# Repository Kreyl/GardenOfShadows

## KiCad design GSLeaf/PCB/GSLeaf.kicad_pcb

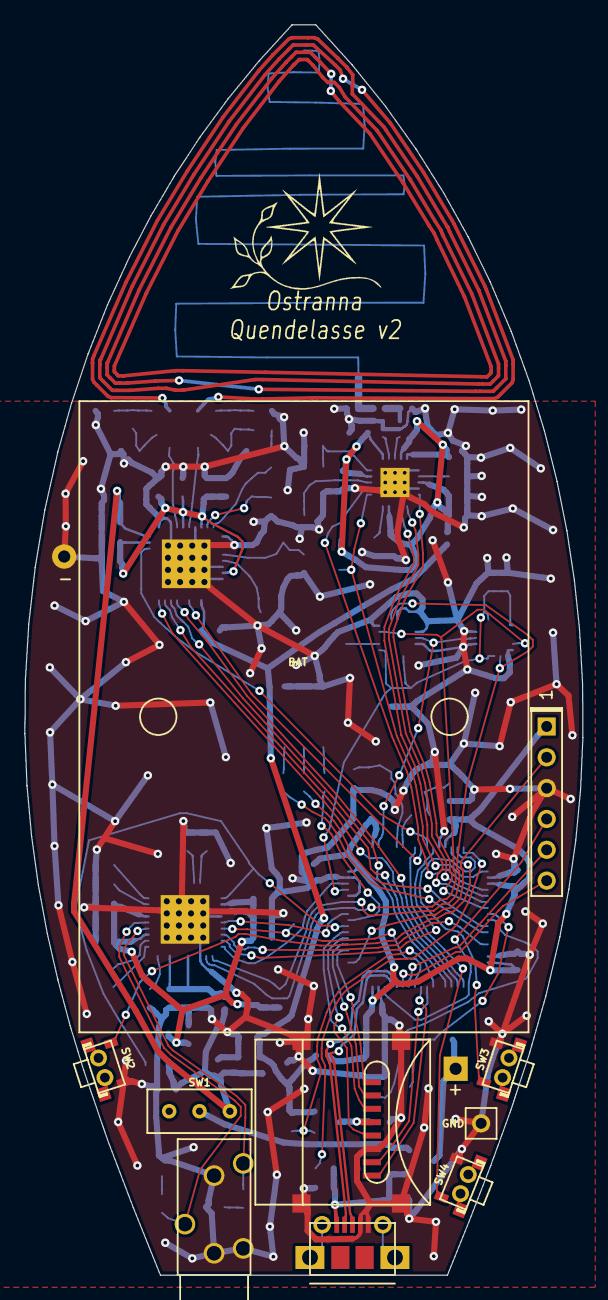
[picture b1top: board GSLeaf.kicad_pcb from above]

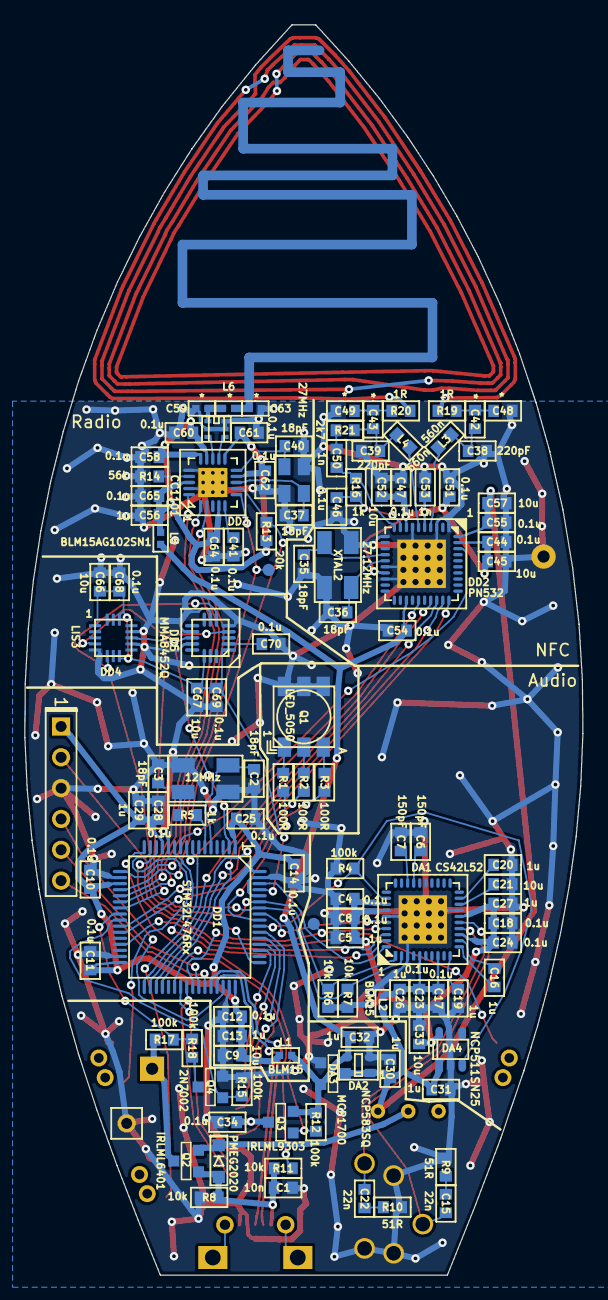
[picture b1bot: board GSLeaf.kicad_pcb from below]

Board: 2 copper layers, 46.0 x 103.0 mm, 129 parts (119 on the bottom side), 94 nets.

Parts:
ANT1: ANT_PCB_MONO; ANT_868_SEIDHE
B1: BAT; BATTERY_AAA_X3
BLN1: BALUN868JOHANSON; BALUN_JOHANSON868
C1: 10n; CAP_0603
C2, C3, C35, C36, C37, C40: 18pF; CAP_0603
C4, C8, C10, C11, C12, C14, C17, C18, C23, C24, C25, C28, C34, C41, C44, C46, C47, C51, C54, C55, C58, C60, C61, C62, C64, C65, C68, C69, C70: 0.1u; CAP_0603
C5, C13, C16, C19, C20, C26, C27, C29, C30, C31, C32, C56: 1u; CAP_0603
C6, C7: 150pF; CAP_0603
C9, C21, C33, C45, C52, C57, C66, C67: 10u; CAP_0603
C15, C22: 22n; CAP_0603
C38, C39: 220pF; CAP_0603
C42, C43, C48, C49: *; CAP_0603
C50, C53: 1n; CAP_0603
C59, C63: *; CAP_0402
D1: PMEG2020; SOD323
DA1: CS42L52; QFN40
DA2: NCP583SQ; SC82AB
DA3: MCP1700; SOT23-3
DA4: NCP511SN25; SOT23-5
DD1: STM32L476Rx; LQFP64
DD2: PN532; QFN40
DD3: CC1101; QFN20
DD4: LIS3; LGA16_3X3_5_3
DD5: MMA8452Q; QFN16_5x3
L1, L2: BLM15; IND_0402
L3, L4: 560n; IND_0603
L5: BLM15AG102SN1; IND_0402
L6: *; IND_0402
Logo1: Logo; Ostranna_12d7_10d1
Q1: LED_5050
Q2: IRLML6401; SOT23-3
Q3: IRLML9303; SOT23-3
Q4: 2N7002; SOT23-3
R1, R2, R3: 100R; RES_0603
R4, R12, R15, R17, R18: 100k; RES_0603
R5, R16: 1k; RES_0603
R6, R7, R8, R11: 10k; RES_0603
R9, R10: 51R; RES_0603
R13: 20k; RES_0603
R14: 56k; RES_0603
R19, R20: 1R; RES_0603
R21: 2k7; RES_0603
SW1: SWITCH; SW_SS-1P2T
SW2, SW3, SW4: BTN; BTN_IT1198
TP1, TP2: TESTPOINT; TESTPOINT_1MM
XL1: CONN_6; PLS-6
XL2: USB_MINI_B; USBmicro_MOLEX_1050170001
XL3: AudioJackSimple; AUDIO_CKX3_5_30
XL4: CONN_MICROSD; MICROSD_CAP_FIX05A
XL5: CONN_1; PLS-1Rnd
XTAL1: 12MHz; 0503x4-4
XTAL2: 27.12MHz; 0503x4-4
XTAL3: 27MHz; 03225C4

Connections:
+3.3V: C32.1, C54.1, DA2.3, DA3.2, DD2.23, L1.2, L5.2, Q3.2, R12.1
+5V: C1.2, D1.A, Q2.1, R8.1, R11.2, XL2.1
+BATT: B1.A, Q2.3, R17.1
/ACC_INT1: DD1.2, DD4.11, DD5.11
/ACC_PWR: C66.1, C67.1, C68.1, C69.1, DD1.61, DD4.1, DD4.14, DD5.1, DD5.14
/ANT1: BLN1.1, C59.1, L6.2
/ANT01: DD2.4, L3.2
/ANT2: ANT1.1, C63.1, L6.1
/ANT02: DD2.6, L4.2
/AU_LRCK: DA1.40, DD1.62
/AU_MCLK: DA1.37, DD1.41, TP1.1
/AU_RST: DA1.32, DA4.3, DD1.55, R4.2
/AU_SCLK: DA1.38, DD1.29
/AU_SDIN: DA1.39, DD1.11
/AU_SDOUT: DA1.36, DD1.57
/Antenna: R19.2, R20.2
/BAT_MEAS: DD1.24, R17.2, R18.1
/BLUE_LED: DD1.56, R1.2
/BTN_COM: DD1.14, SW2.1
/BTN_DOWN: DD1.8, SW4.1
/BTN_UP: DD1.15, SW3.1
/CC_CS: DD1.20, DD3.7, R13.1
/CC_GDO0: DD1.17, DD3.6, TP2.1
/CC_MISO: DD1.22, DD3.2
/CC_MOSI: DD1.23, DD3.20
/CC_SCK: DD1.21, DD3.1
/D+: DD1.45, XL2.3
/D-: DD1.44, XL2.2
/GREEN_LED: DD1.27, R3.2
/HP_OUTA: C15.2, DA1.15, XL3.2
/HP_OUTB: C22.2, DA1.14, XL3.3
/MEASURE_EN: DD1.25, Q4.1, R15.2
/PN_IRQ: DD1.9, DD2.25
/PN_MISO: DD1.35, DD2.29
/PN_MOSI: DD1.36, DD2.28
/PN_NSS: DD1.33, DD2.27
/PN_RESET: DD1.10, DD2.38
/PN_SCK: DD1.34, DD2.30
/PN_VDD: C44.1, C45.1, C47.1, C51.1, C52.1, C53.1, DD2.5, DD2.8, DD2.17, DD2.39
/PWR_UNST_ALWAYS: D1.C, Q2.2, SW1.2
/RED_LED: DD1.26, R2.2
/RF1: BLN1.4, DD3.12
/RF2: BLN1.3, DD3.13
/RX_NET: C39.2, C43.2, L4.1, R21.2
/SCL: DA1.2, DD1.58, DD4.4, DD5.4, R7.1
/SDA: DA1.1, DD1.59, DD4.6, DD5.6, R6.1
/SD_CLK: DD1.53, XL4.5
/SD_CMD: DD1.54, XL4.3
/SD_DAT0: DD1.39, XL4.7
/SD_DAT1: DD1.40, XL4.8
/SD_DAT2: DD1.51, XL4.1
/SD_DAT3: DD1.52, XL4.2
/SD_PWR: C34.1, Q3.3, XL4.4
/SD_PWR_EN: DD1.38, Q3.1, R12.2
/SWCLK: DD1.49, XL1.2
/SWDIO: DD1.46, XL1.4
/UART_RX: DD1.43, XL1.6
/UART_TX: DD1.42, XL1.5
GND: B1.C, BLN1.2, BLN1.5, BLN1.6, C1.1, C2.2, C3.2, C4.2, C5.2, C6.1, C7.1, C8.2, C9.1, C10.1, C11.1, C12.1, C13.1, C14.1, C17.2, C18.2, C19.1, C20.1, C21.1, C23.2, C24.2, C25.1, C26.2, C27.2, C28.1, C29.1, C30.2, C31.2, C32.2, C33.2, C34.2, C35.2, C36.2, C37.2, C38.2, C39.1, C40.2, C41.1, C44.2, C45.2, C46.2, C47.2, C48.2, C49.1, C51.2, C52.2, C53.2, C54.2, C55.2, C56.2, C57.2, C58.2, C59.2, C60.2, C61.2, C62.2, C63.2, C64.2, C65.2, C66.2, C67.2, C68.2, C69.2, C70.2, DA1.3, DA1.17, DA1.35, DA1.PAD, DA2.2, DA3.1, DA4.2, DD1.12, DD1.18, DD1.31, DD1.47, DD1.60, DD1.63, DD2.1, DD2.3, DD2.7, DD2.11, DD2.16, DD2.18, DD2.PAD, DD3.16, DD3.19, DD3.PAD, DD4.5, DD4.10, DD4.12, DD5.5, DD5.7, DD5.10, DD5.12, Q1.4, Q1.5, Q1.6, Q4.2, R4.1, R8.2, R9.1, R10.1, R14.2, R15.1, SW2.2, SW3.2, SW4.2, XL1.3, XL2.4, XL2.5, XL3.1, XL3.H, XL4.6, XL4.H, XL5.1, XTAL1.H, XTAL2.H, XTAL3.H
unnamed: C2.1, DD1.5, XTAL1.1
unnamed: C3.1, R5.1, XTAL1.2
unnamed: C6.2, DA1.27
unnamed: C7.2, DA1.28
unnamed: C15.1, R9.2
unnamed: C16.1, DA1.11
unnamed: C16.2, DA1.12
unnamed: C17.1, C23.1, C26.1, DA1.5, DA1.8, L2.2
unnamed: C19.2, DA1.10
unnamed: C20.2, DA1.19
unnamed: C21.2, DA1.18
unnamed: C22.1, R10.2
unnamed: C35.1, DD2.14, XTAL2.1
unnamed: C36.1, DD2.15, XTAL2.2
unnamed: C37.1, DD3.8, XTAL3.1
unnamed: C38.1, C42.2, L3.1
unnamed: C40.1, DD3.10, XTAL3.2
unnamed: C41.2, DD3.5
unnamed: C42.1, C48.1, R19.1
unnamed: C43.1, C49.2, R20.1
unnamed: C46.1, DD2.9, R16.1
unnamed: C50.1, DD2.10, R16.2
unnamed: C50.2, R21.1
unnamed: C70.1, DD5.2
unnamed: DD1.6, R5.2
unnamed: DD1.16, R11.1
unnamed: DD3.17, R14.1
unnamed: Q1.1, R1.1
unnamed: Q1.2, R2.1
unnamed: Q1.3, R3.1
unnamed: Q4.3, R18.2
PwrMCU: C9.2, C10.2, C11.2, C12.2, C13.2, C14.2, C25.2, C28.2, C29.2, DD1.1, DD1.13, DD1.19, DD1.32, DD1.48, DD1.64, DD4.7, DD4.8, L1.1, XL1.1
PwrUnst: C30.1, C31.1, C55.1, C57.1, DA2.1, DA2.4, DA3.3, DA4.1, DD2.40, L2.1, SW1.1
VAA: C4.1, C5.1, C8.1, C18.1, C24.1, C27.1, C33.1, DA1.13, DA1.16, DA1.33, DA1.34, DA4.5, R6.2, R7.2
VCC: C56.1, C58.1, C60.1, C61.1, C62.1, C64.1, C65.1, DD3.4, DD3.9, DD3.11, DD3.14, DD3.15, DD3.18, L5.1, R13.2

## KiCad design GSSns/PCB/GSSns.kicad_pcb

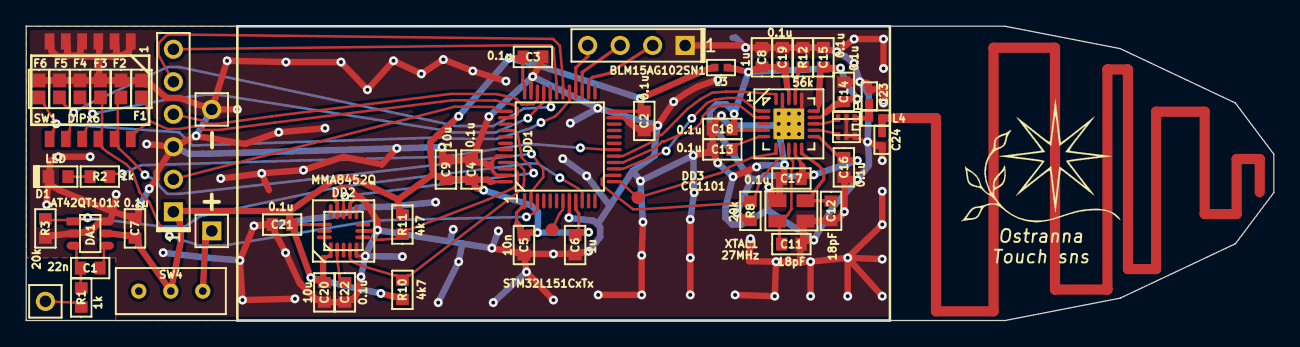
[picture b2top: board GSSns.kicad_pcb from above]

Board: 2 copper layers, 97.5 x 23.0 mm, 56 parts (0 on the bottom side), 41 nets.

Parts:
ANT1: ANT_PCB_MONO; ANT_868_SEIDHE
BLN1: BALUN868JOHANSON; BALUN_JOHANSON868
C1: 22n; CAP_0603
C2, C3, C4, C7, C13, C14, C15, C16, C17, C18, C19, C21, C22: 0.1u; CAP_0603
C5: 10n; CAP_0603
C6, C8: 1u; CAP_0603
C9, C20: 10u; CAP_0603
C11, C12: 18pF; CAP_0603
C23, C24: *; CAP_0402
D1: LED; LED_0603
DA1: AT42QT101x; SOT23-6
DD1: STM32L151CxTx; LQFP48
DD2: MMA8452Q; QFN16_5x3
DD3: CC1101; QFN20
F1, F2, F3, F4, F5, F6: Fuse0R; RES_0603_FUSE
L3: BLM15AG102SN1; IND_0402
L4: *; IND_0402
Logo1: Logo; Ostranna_12d7_10d1
R1, R2: 1k; RES_0603
R3, R8: 20k; RES_0603
R10, R11: 4k7; RES_0603
R12: 56k; RES_0603
SW1: DIPx6; DIP_SMD_1D27X6
SW4: SWITCH; SW_SS-1P2T
TP1, TP2: TESTPOINT; TESTPOINT_1MM
XL1: CONN_6; PLS-6
XL2, XL4: CONN_1; PLS-1Rnd
XL3: CONN_1; PLS-1Square
XL5: CONN_4; PLS-4
XTAL1: 27MHz; 03225C4

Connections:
+BATT: C2.1, C3.1, C4.1, C5.1, C6.1, C7.1, C9.2, C20.1, C21.1, DA1.5, DD1.1, DD1.9, DD1.24, DD1.36, DD1.48, DD2.1, DD2.14, L3.2, R10.1, R11.2, SW4.2, XL1.1
/ACC_INT1: DD1.40, DD2.11
/ANT1: BLN1.1, C23.1, L4.2
/ANT2: ANT1.1, C24.1, L4.1
/BAT_IN: SW4.1, XL3.1
/CC_CS: DD1.14, DD3.7, R8.1
/CC_GDO0: DD1.13, DD3.6, TP2.1
/CC_MISO: DD1.16, DD3.2
/CC_MOSI: DD1.17, DD3.20
/CC_SCK: DD1.15, DD3.1
/DS1: DD1.38, F1.2, SW1.12
/DS2: DD1.2, F2.2, SW1.11
/DS3: DD1.3, F3.2, SW1.10
/DS4: DD1.33, F4.2, SW1.9
/DS5: DD1.32, F5.2, SW1.8
/DS6: DD1.29, F6.2, SW1.7
/I2C_SCL: DD1.45, DD2.4, R10.2
/I2C_SDA: DD1.46, DD2.6, R11.1
/RF1: BLN1.4, DD3.12
/RF2: BLN1.3, DD3.13
/SNS: DA1.1, DD1.10, R3.1
/SWCLK: DD1.37, XL1.2
/SWDIO: DD1.34, XL1.4
/UART_RX: DD1.31, XL1.6
/UART_TX: DD1.30, XL1.5
GND: BLN1.2, BLN1.5, BLN1.6, C2.2, C3.2, C4.2, C5.2, C6.2, C7.2, C8.2, C9.1, C11.2, C12.2, C13.1, C14.2, C15.2, C16.2, C17.2, C18.2, C19.2, C20.2, C21.2, C22.2, C23.2, C24.2, D1.C, DA1.2, DA1.6, DD1.8, DD1.23, DD1.35, DD1.44, DD1.47, DD2.5, DD2.7, DD2.10, DD2.12, DD3.16, DD3.19, DD3.PAD, F1.1, F2.1, F3.1, F4.1, F5.1, F6.1, R3.2, R12.2, SW1.1, SW1.2, SW1.3, SW1.4, SW1.5, SW1.6, XL1.3, XL4.1, XL5.1, XTAL1.H
unnamed: C1.1, DA1.3, R1.2
unnamed: C1.2, DA1.4
unnamed: C11.1, DD3.8, XTAL1.1
unnamed: C12.1, DD3.10, XTAL1.2
unnamed: C13.2, DD3.5
unnamed: C22.1, DD2.2
unnamed: D1.A, R2.2
unnamed: DD1.7, TP1.1
unnamed: DD1.18, R2.1
unnamed: DD1.26, XL5.2
unnamed: DD1.27, XL5.3
unnamed: DD1.28, XL5.4
unnamed: DD3.17, R12.1
unnamed: R1.1, XL2.1
VCC: C8.1, C14.1, C15.1, C16.1, C17.1, C18.1, C19.1, DD3.4, DD3.9, DD3.11, DD3.14, DD3.15, DD3.18, L3.1, R8.2

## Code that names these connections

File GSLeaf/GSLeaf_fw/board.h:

/*
 * board.h
 *
 *  Created on: 12 ����. 2015 �.
 *      Author: Kreyl
 */

#pragma once

// ==== General ====
#define BOARD_NAME          "GSLeaf01"
#define APP_NAME            "CSTest"

// MCU type as defined in the ST header.
#define STM32L476xx

// Freq of external crystal if any. Leave it here even if not used.
#define CRYSTAL_FREQ_HZ         12000000

// OS timer settings
#define STM32_ST_IRQ_PRIORITY   2
#define STM32_ST_USE_TIMER      5
#define SYS_TIM_CLK             (Clk.APB1FreqHz)    // Timer 5 is clocked by APB1

//  Periphery
#define I2C1_ENABLED            TRUE
#define I2C2_ENABLED            FALSE
#define I2C3_ENABLED            FALSE
#define SIMPLESENSORS_ENABLED   FALSE
#define BUTTONS_ENABLED         FALSE

#define ADC_REQUIRED            FALSE

#if 1 // ========================== GPIO =======================================
// EXTI
#define INDIVIDUAL_EXTI_IRQ_REQUIRED    FALSE

// Sensor
#define SNS_PIN         GPIOB, 15, pudPullDown

// UART
#define UART_GPIO       GPIOA
#define UART_TX_PIN     9
#define UART_RX_PIN     10
#define UART_AF         AF7 // for all USARTs

// RGB LED
#define LED_BLUE_CH     { GPIOB, 4, TIM3, 1, invNotInverted, omPushPull, 255 }
#define LED_GREEN_CH    { GPIOB, 1, TIM3, 4, invNotInverted, omPushPull, 255 }
#define LED_RED_CH      { GPIOB, 0, TIM3, 3, invNotInverted, omPushPull, 255 }

// PWR_EN
#define PWR_EN_PIN      GPIOA, 15, omPushPull
// Charge
#define CHARGE_PIN      GPIOB, 11, pudPullUp

// CS42L52
#define AU_RESET        GPIOB, 3, omPushPull
#define AU_SDIN         GPIOC, 3, omPushPull, pudNone, AF13 // MOSI; SAI1_A
#define AU_SDOUT        GPIOB, 5, omPushPull, pudNone, AF13 // MISO; SAI1_B
#define AU_MCLK         GPIOB, 8, omPushPull, pudNone, AF13
#define AU_MCLK_TIM     GPIOB, 8, TIM4, 3, invNotInverted, omPushPull, 1
#define AU_LRCK         GPIOB, 9, omPushPull, pudNone, AF13
#define AU_SCLK         GPIOB, 10, omPushPull, pudNone, AF13
#define AU_i2c          i2c1
#define AU_SAI          SAI1
#define AU_SAI_A        SAI1_Block_A
#define AU_SAI_B        SAI1_Block_B
#define AU_SAI_RccEn()  RCC->APB2ENR |= RCC_APB2ENR_SAI1EN

// I2C
#define I2C1_GPIO       GPIOB
#define I2C1_SCL        6
#define I2C1_SDA        7
#define I2C2_GPIO       GPIOB
#define I2C2_SCL        10
#define I2C2_SDA        11
#define I2C3_GPIO       GPIOC
#define I2C3_SCL        0
#define I2C3_SDA        1
// I2C Alternate Function
#define I2C_AF          AF4

// SD
#define SD_PWR_PIN      GPIOC, 7
#define SD_AF           AF12
#define SD_DAT0         GPIOC,  8, omPushPull, pudPullUp, SD_AF
#define SD_DAT1         GPIOC,  9, omPushPull, pudPullUp, SD_AF
#define SD_DAT2         GPIOC, 10, omPushPull, pudPullUp, SD_AF
#define SD_DAT3         GPIOC, 11, omPushPull, pudPullUp, SD_AF
#define SD_CLK          GPIOC, 12, omPushPull, pudNone,   SD_AF
#define SD_CMD          GPIOD,  2, omPushPull, pudPullUp, SD_AF

// Radio: SPI, PGpio, Sck, Miso, Mosi, Cs, Gdo0
#define CC_Setup0       SPI1, GPIOA, 5,6,7, GPIOA,4, GPIOA,3

#endif // GPIO

#if 1 // =========================== SPI =======================================
#define CC_SPI          SPI1
#define CC_SPI_AF       AF5
#endif

#if 1 // =========================== I2C =======================================
// i2cclkPCLK1, i2cclkSYSCLK, i2cclkHSI
#define I2C_CLK_SRC     i2cclkHSI
#define I2C_BAUDRATE_HZ 400000
#endif

#if ADC_REQUIRED // ======================= Inner ADC ==========================
// Clock divider: clock is generated from the APB2
#define ADC_CLK_DIVIDER		adcDiv2

// ADC channels
#define ADC_BATTERY_CHNL 	14
// ADC_VREFINT_CHNL
#define ADC_CHANNELS        { ADC_BATTERY_CHNL, ADC_VREFINT_CHNL }
#define ADC_CHANNEL_CNT     2   // Do not use countof(AdcChannels) as preprocessor does not know what is countof => cannot check
#define ADC_SAMPLE_TIME     ast24d5Cycles
#define ADC_OVERSAMPLING_RATIO  64   // 1 (no oversampling), 2, 4, 8, 16, 32, 64, 128, 256
#endif

#if 1 // =========================== DMA =======================================
#define STM32_DMA_REQUIRED  TRUE
// ==== Uart ====
#define UART_DMA_TX_MODE(Chnl) (STM32_DMA_CR_CHSEL(Chnl) | DMA_PRIORITY_LOW | STM32_DMA_CR_MSIZE_BYTE | STM32_DMA_CR_PSIZE_BYTE | STM32_DMA_CR_MINC | STM32_DMA_CR_DIR_M2P | STM32_DMA_CR_TCIE)
#define UART_DMA_RX_MODE(Chnl) (STM32_DMA_CR_CHSEL(Chnl) | DMA_PRIORITY_MEDIUM | STM32_DMA_CR_MSIZE_BYTE | STM32_DMA_CR_PSIZE_BYTE | STM32_DMA_CR_MINC | STM32_DMA_CR_DIR_P2M | STM32_DMA_CR_CIRC)
#define UART_DMA_TX     STM32_DMA_STREAM_ID(1, 4)
#define UART_DMA_RX     STM32_DMA_STREAM_ID(1, 5)
#define UART_DMA_CHNL   2

// ==== I2C ====
#define I2C1_DMA_TX     STM32_DMA_STREAM_ID(2, 7)
#define I2C1_DMA_RX     STM32_DMA_STREAM_ID(2, 6)
#define I2C1_DMA_CHNL   5
#define I2C2_DMA_TX     STM32_DMA_STREAM_ID(1, 4)
#define I2C2_DMA_RX     STM32_DMA_STREAM_ID(1, 5)
#define I2C2_DMA_CHNL   3
#define I2C3_DMA_TX     STM32_DMA_STREAM_ID(1, 2)
#define I2C3_DMA_RX     STM32_DMA_STREAM_ID(1, 3)
#define I2C3_DMA_CHNL   3

// ==== SAI ====
#define SAI_DMA_A       STM32_DMA_STREAM_ID(2, 1)
#define SAI_DMA_B       STM32_DMA_STREAM_ID(2, 2)
#define SAI_DMA_CHNL    1

// ==== SDMMC ====
#define STM32_SDC_SDMMC1_DMA_STREAM   STM32_DMA_STREAM_ID(2, 5)

#if ADC_REQUIRED
#define ADC_DMA         STM32_DMA1_STREAM1
#define ADC_DMA_MODE    STM32_DMA_CR_CHSEL(0) |   /* DMA1 Stream1 Channel0 */ \
                        DMA_PRIORITY_LOW | \
                        STM32_DMA_CR_MSIZE_HWORD | \
                        STM32_DMA_CR_PSIZE_HWORD | \
                        STM32_DMA_CR_MINC |       /* Memory pointer increase */ \
                        STM32_DMA_CR_DIR_P2M |    /* Direction is peripheral to memory */ \
                        STM32_DMA_CR_TCIE         /* Enable Transmission Complete IRQ */
#endif // ADC

#endif // DMA

#if 1 // ========================== USART ======================================
#define PRINTF_FLOAT_EN TRUE
#define UART_TXBUF_SZ   4096
#define UART_RXBUF_SZ   1024
#define CMD_BUF_SZ      1024

#define CMD_UART        USART1

#define CMD_UART_PARAMS \
    CMD_UART, UART_GPIO, UART_TX_PIN, UART_GPIO, UART_RX_PIN, \
    UART_DMA_TX, UART_DMA_RX, UART_DMA_TX_MODE(UART_DMA_CHNL), UART_DMA_RX_MODE(UART_DMA_CHNL), \
    uartclkHSI // Use independent clock
#endif

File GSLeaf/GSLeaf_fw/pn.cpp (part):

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#endif
    // ==== GPIO ====
    PinSetupOut(PN_RST_PIN, omPushPull);
    PinSetupOut(PN_NSS_PIN, omPushPull);
    PinSetupAlterFunc(PN_SCK_PIN);
    PinSetupAlterFunc(PN_MISO_PIN);
    PinSetupAlterFunc(PN_MOSI_PIN);
    IRstLo();
    INssHi();

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
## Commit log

2017-05-31 + GS Sns sent to production
2017-06-05 Minor changes in TopoR
2017-06-05 + Leaf layout done
2017-06-06 Leaf sent to factory
2017-06-10 + Sns antenna matched
2017-06-22 Leaf speaks "alive" out of flash
2017-06-22 Alive.wav opened
2017-06-23 Alive.wav played ok
2017-06-23 + both 16000 and 44100 plays at normal speed
2017-06-23 Single buf, lags
2017-06-23 16000, 44100, 48000, 96000 ok
2017-06-24 Switch to 24MHz
2017-06-24 +Btns
2017-06-25 + Antenna matched
2017-06-25 + Speaks "Alive" aloud
2017-06-25 + Volume works
2017-06-26 + Acc
2017-06-26 + Stop + PlayEnd evt
2017-06-26 Clean-up
2017-06-26 Acc logic done
2017-06-26 Works ok
2017-06-26 + Audio standby => 10mA
2017-06-26 + Volume and pause inside Settings.ini
2017-06-26 + GSSns transmits something
2017-06-28 + Sns acc
2017-06-28 + CC works + Test sounds
2017-06-28 + Play logic
2017-06-28 + Volume up/down
2017-06-28 + Fadeout
2017-06-28 + Surround plays al over time * FadeOut put into player's thread
2017-06-28 * Getvolume
2017-06-28 + Charging indication
2017-06-28 * DirName made global to eliminate eventual stack overflow
2017-06-29 Filename moved to global and increased
2017-07-03 Release
2017-07-16 New leaf sch nearly ready
2017-07-17 Layout made by half
2017-07-17 Layout done
2017-07-17 Tracing in progress
2017-07-18 Sent to factory
2017-07-25 * First commit of new system (17.6.0) on new board. Uart works.
2017-07-27 pn under construction
2017-07-30 Card appearence and loss implemented
2017-07-31 * Minor PN cleanup + Main task card evts
2017-07-31 i2c ok, fighting with sd
2017-07-31 Music plays ok (24 MHz only)
2017-07-31 + Play dir by card ID implemented
2017-07-31 Loading table.csv implemented
2017-07-31 + buttons
2017-08-01 * Bug of repeating last custom sound
2017-08-15 + Blink when touch Release
2019-03-15 + Sound Ondolindeva
2019-06-06 Switching to allnew
2019-06-06 Compiled ok, UART works
2019-06-08 * switch to Audioplayer by @tagunil Works ok
2019-06-08 First version of logic.
2019-06-08 Logic seems ok
2019-06-08 + Radio init ok
2019-06-08 + Radio xchange works
2019-08-03 - wavs
2019-08-04 + Acc Acc Average implemented
2019-08-04 Speaks ok
2019-08-04 + config read from ini file RC
2019-08-10 Still no sns
2019-08-11 + sns
2019-08-11 * gitignore
2019-08-11 * Fix: volume is now really controlled
2019-08-11 * Volume controlled by config
2020-09-02 Switch to CubeIDE
2021-07-17 * Switch to CubeIDE
